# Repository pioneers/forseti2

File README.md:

forseti2
========
forseti2 (Named after the Norse god of justice) is PiE's third* iteration of a Field Control software. It has been in use from 2014-2017, with substantial changes along the way.

## Deploying Driver Stations
Driver Stations can be downloaded from PieCentral's [Releases section](https://github.com/pioneers/PieCentral/releases), or built locally using the `dawn/fieldcontrol` branch.

### Installing for MacOS and GNU/Linux
 1. Download the `darwin-x64` or `linux-x64` release anywhere (preferably desktop)
 2. In Terminal, run `driver_station.sh`
 3. Run Field Control Dawn

### Installing for Windows
 1. Download the `win32-ia32` release anywhere
 2. On the Desktop:
   * Create the file `bridge_address.txt` and write the Controller's IP address
   * Create the file `station_number.txt` and write the station number you want to be (0, 1, 2, 3 => blue1, blue2, gold1, gold2)
 3. Run Field Control Dawn

## Deploying Field Controller
forseti2 is dependent on external libraries, so there will be some OS-dependent instructions.

### [Lightweight Communications and Marshalling (LCM)](https://lcm-proj.github.io/)
1. Follow Online instructions on how to build it on your system.
2. Once LCM is built, move `lcm.jar` into the forseti2 directory to take advantage of `lcm-spy.sh` packet introspection.

### Installing for Ubuntu and MacOS
1. Install LCM as detailed above
2. If Ubuntu, also run:
```bash
sudo apt-get install arduino;
sudo pip install pyfirmata;
```

## Nodes
### timer.py
Maintains match state (timer and robot states)

#### Inputs
* Match/Init: Match
  * Resets match timer when a new match is initialized
* Timer/Control: TimeControl
  * Receives commands for the match timer (start, pause, reset)
* Robot[0-3]/Estop: Estop
  * Uses current emergency stop state and overrides all robot state if in estop mode
* Robot[0-3]/Override: Override
  * Determines whether or not robot is in manual override mode (overrides timers for manual operation)
* Robot[0-3]/RobotState: RobotState
  * Sets robot state using manual override only if in override mode

#### Outputs
* Timer/Time: Time
  * Publishes (every .3 secs) time elapsed in current match and stage, as well as the current stage name
* Robot[0-3]/RobotControl: RobotControl
  * Publishes (every .3 secs) the state of the robot (estop?, autonomous?, enabled?)

### lcm_ws_bridge.py
Bridges LCM to Websockets so JavaScript applications can access the network

### field_control.py
Manages electronics on the field

#### Inputs
* GameObjectTimer/LighthouseTime: LighthouseTime
  * Uses timer info to determine when to dump balls onto field
* Timer/Time: Time
  * Only dumps balls onto field during teleop and autonomous phases

#### Outputs
* Game_Button[0-1]/Button: Button
  * Publishes (every .3 secs) the state of a button
* Game_Motor[0-1]/Motor: Motor
  * Publishes (every .3 secs) the state of a motor

### heartbeat.py
Heartbeat for clients to confirm they are connected to the field network

#### Outputs
* Heartbeat/Beat: Heartbeat
  * Oscillates between True and False every second?

## Modifications to Dawn
* Listens to a specific Robot[0-3]/RobotControl channel and sends messages to robot accordingly
* Give meaningful feedback to field and students about robot connection status
* Display Field Information
  * Match state and timer
  * Heartbeat
* Manual start disabled in match

## Field Controller Information
### Network Monitor
* Displays live plots of messages/second on each channel

### Judge Console
* Allow score input for current match

### Field Console
* View robot states and allow for manual overriding and estop
* Allow control of match timer and robot enumeration (telling dawn to connect to robots)

### Stream Overlay
* Display field info (like dawn), scores, and upcoming matches

### Audience UI
* Like the stream overlay but as standalone webpage

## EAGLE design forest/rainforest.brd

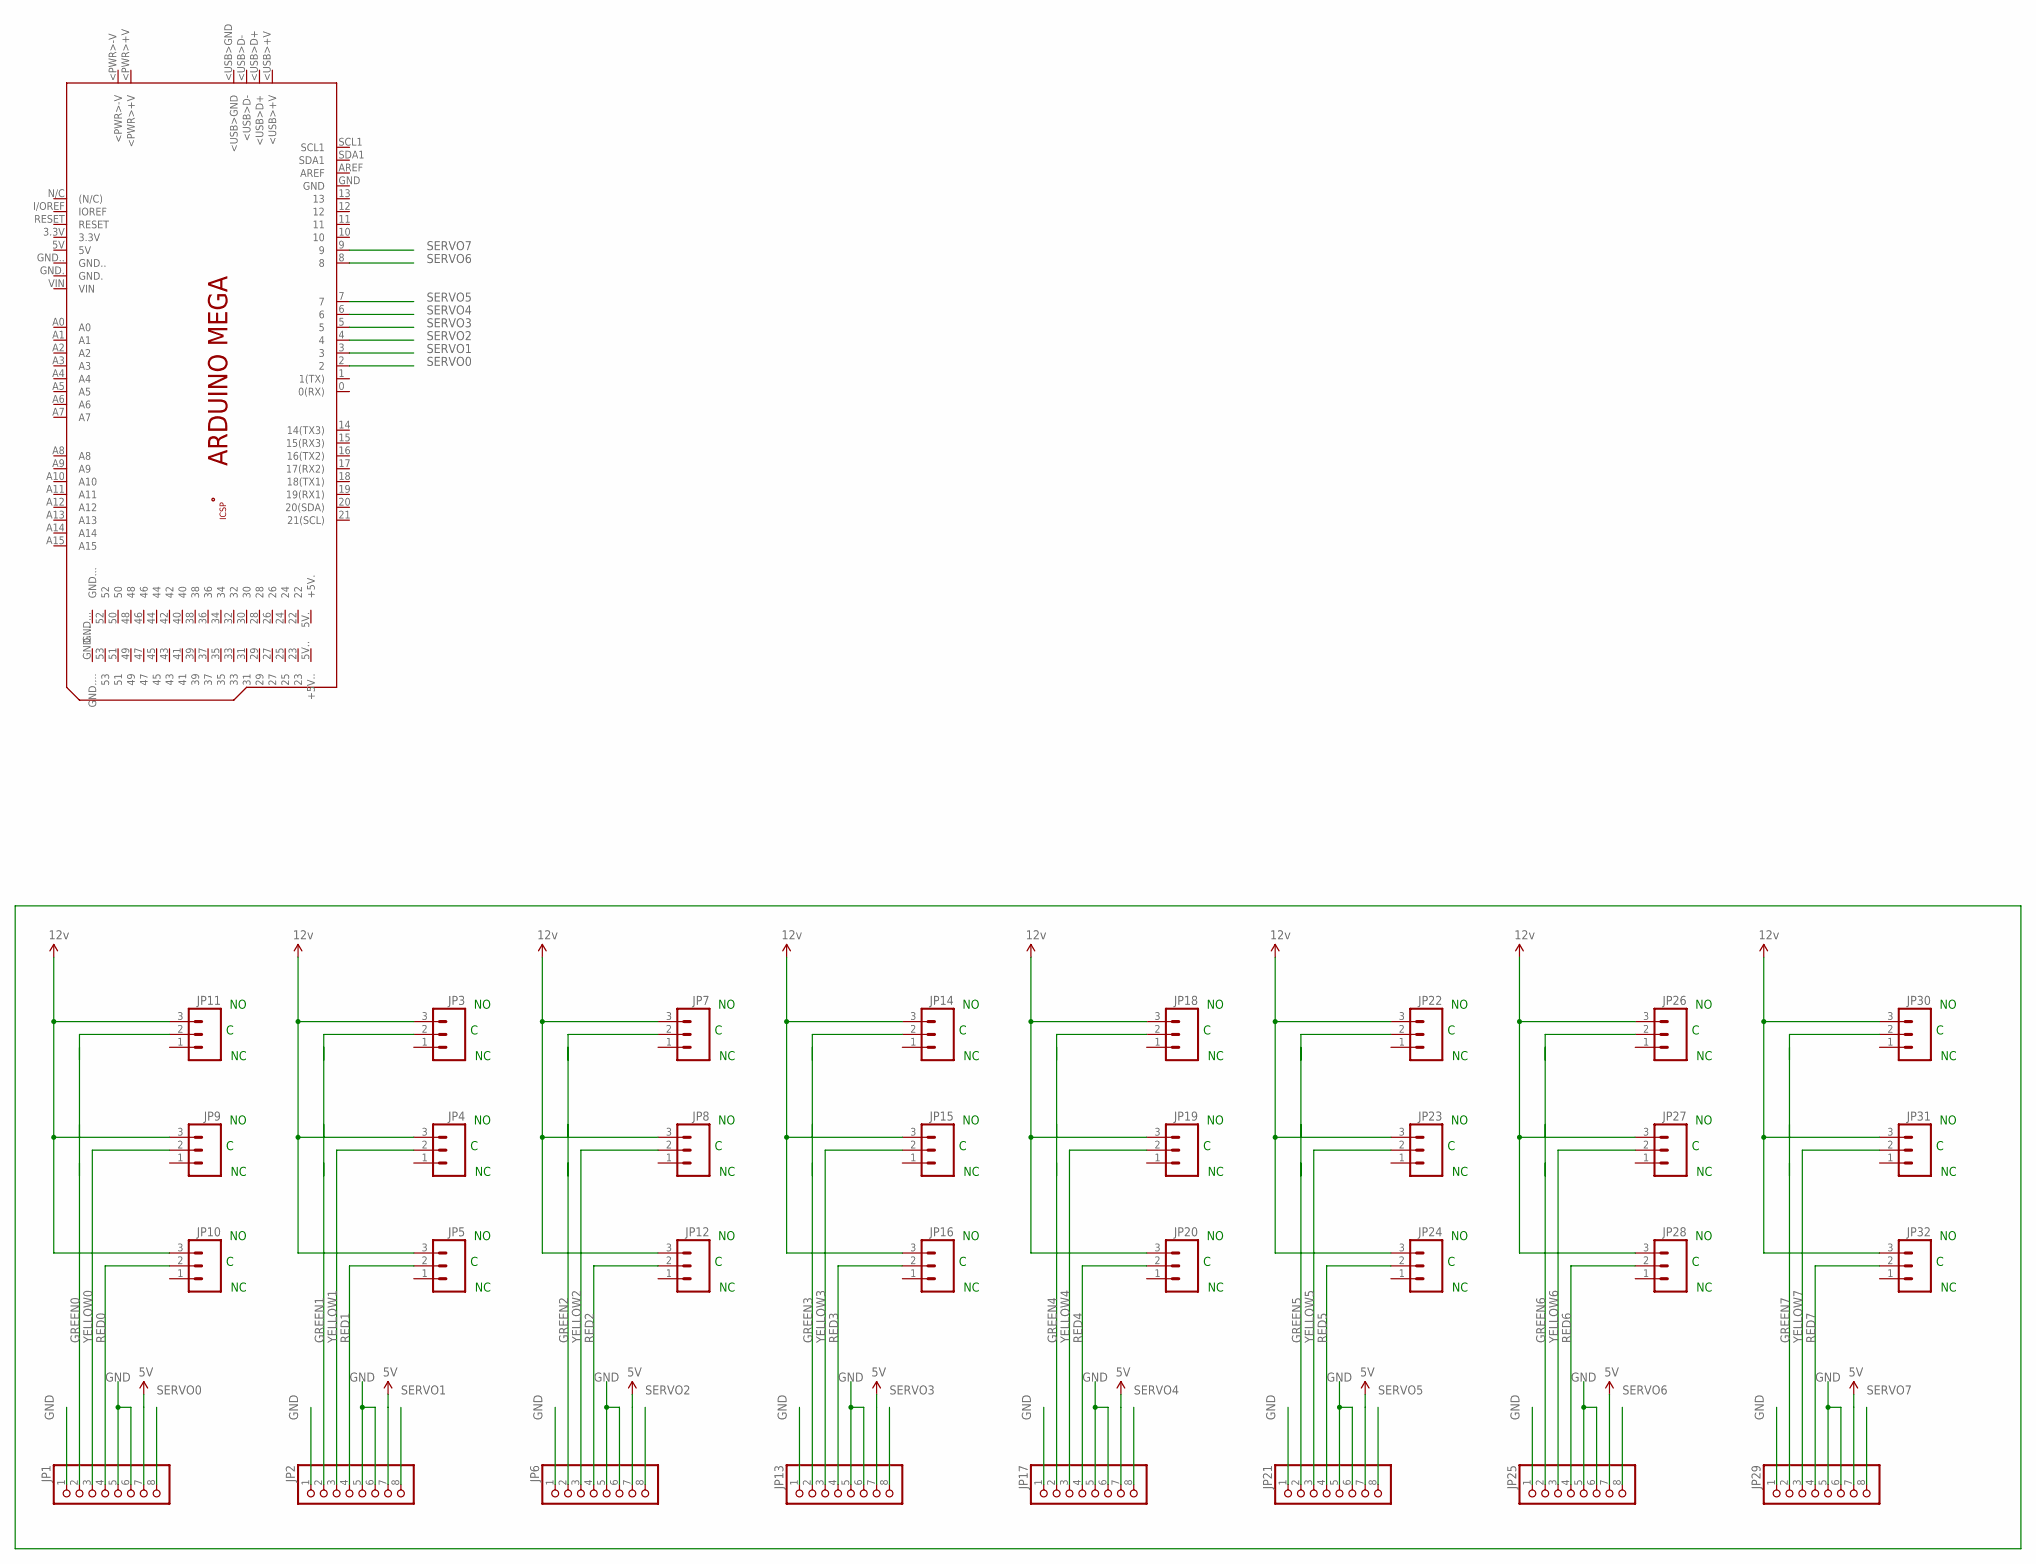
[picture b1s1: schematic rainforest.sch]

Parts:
JP1, JP2, JP6, JP13, JP17, JP21, JP25, JP29: PINHD-1X8; 1X08
JP3, JP4, JP5, JP7, JP8, JP9, JP10, JP11, JP12, JP14, JP15, JP16, JP18, JP19, JP20, JP22, JP23, JP24, JP26, JP27, JP28, JP30, JP31, JP32: M03PTH; 1X03
PCB1: ARDUINO_MEGA

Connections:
5V: JP1.7, JP2.7, JP6.7, JP13.7, JP17.7, JP21.7, JP25.7, JP29.7
12V: JP3.3, JP4.3, JP5.3, JP7.3, JP8.3, JP9.3, JP10.3, JP11.3, JP12.3, JP14.3, JP15.3, JP16.3, JP18.3, JP19.3, JP20.3, JP22.3, JP23.3, JP24.3, JP26.3, JP27.3, JP28.3, JP30.3, JP31.3, JP32.3
GND: JP1.1, JP1.5, JP1.6, JP2.1, JP2.5, JP2.6, JP6.1, JP6.5, JP6.6, JP13.1, JP13.5, JP13.6, JP17.1, JP17.5, JP17.6, JP21.1, JP21.5, JP21.6, JP25.1, JP25.5, JP25.6, JP29.1, JP29.5, JP29.6
GREEN0: JP1.2, JP11.2
GREEN1: JP2.2, JP3.2
GREEN2: JP6.2, JP7.2
GREEN3: JP13.2, JP14.2
GREEN4: JP17.2, JP18.2
GREEN5: JP21.2, JP22.2
GREEN6: JP25.2, JP26.2
GREEN7: JP29.2, JP30.2
RED0: JP1.4, JP10.2
RED1: JP2.4, JP5.2
RED2: JP6.4, JP12.2
RED3: JP13.4, JP16.2
RED4: JP17.4, JP20.2
RED5: JP21.4, JP24.2
RED6: JP25.4, JP28.2
RED7: JP29.4, JP32.2
SERVO0: JP1.8, PCB1.2
SERVO1: JP2.8, PCB1.3
SERVO2: JP6.8, PCB1.4
SERVO3: JP13.8, PCB1.5
SERVO4: JP17.8, PCB1.6
SERVO5: JP21.8, PCB1.7
SERVO6: JP25.8, PCB1.8
SERVO7: JP29.8, PCB1.9
YELLOW0: JP1.3, JP9.2
YELLOW1: JP2.3, JP4.2
YELLOW2: JP6.3, JP8.2
YELLOW3: JP13.3, JP15.2
YELLOW4: JP17.3, JP19.2
YELLOW5: JP21.3, JP23.2
YELLOW6: JP25.3, JP27.2
YELLOW7: JP29.3, JP31.2

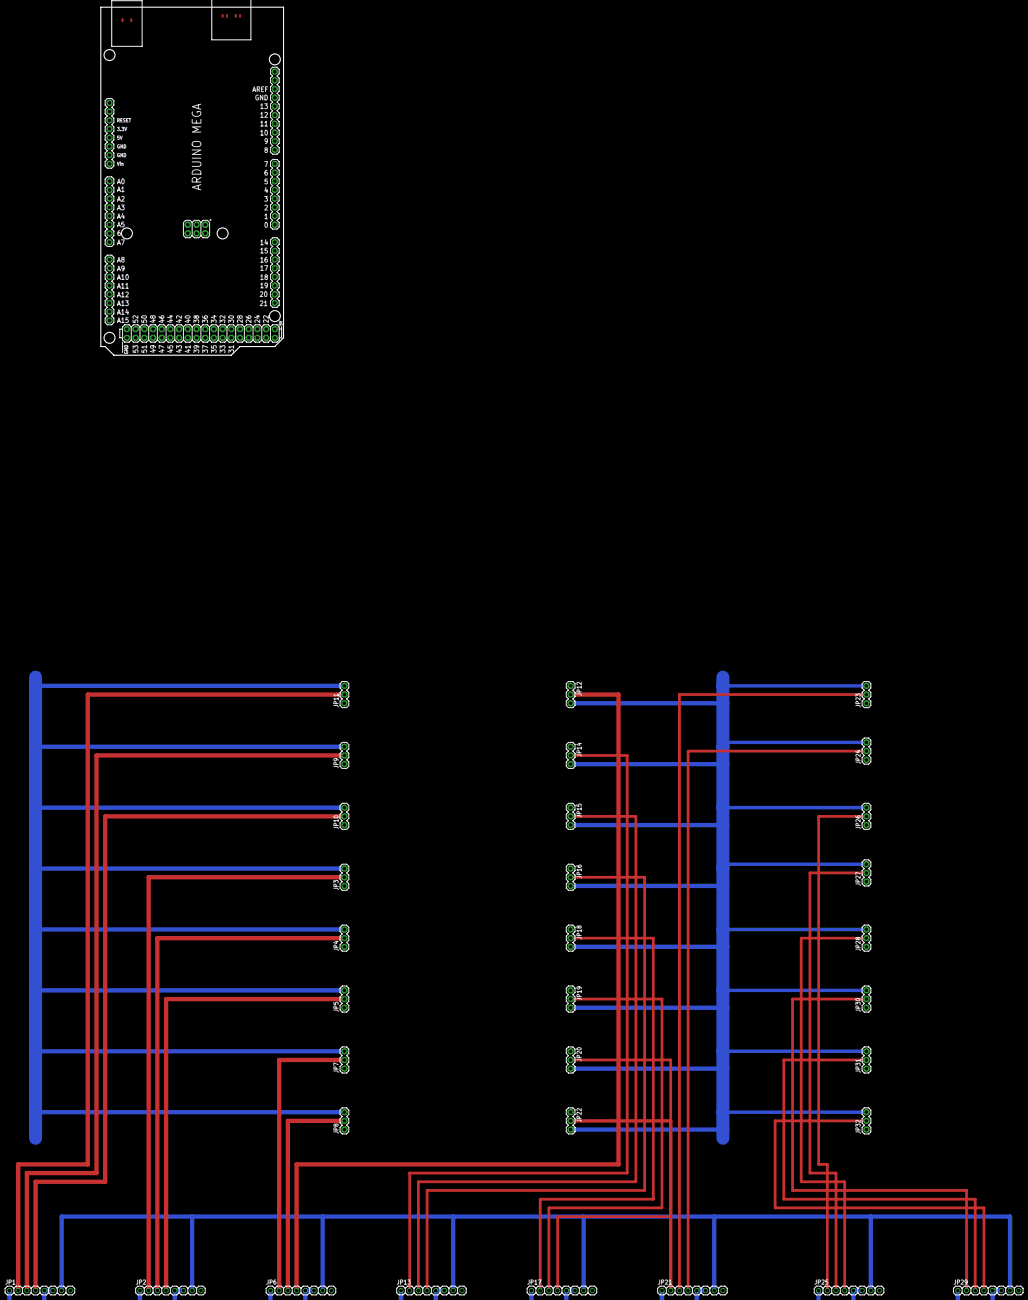
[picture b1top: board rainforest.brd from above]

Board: 2 copper layers, 53.3 x 101.6 mm, 33 parts (0 on the bottom side), 35 nets.

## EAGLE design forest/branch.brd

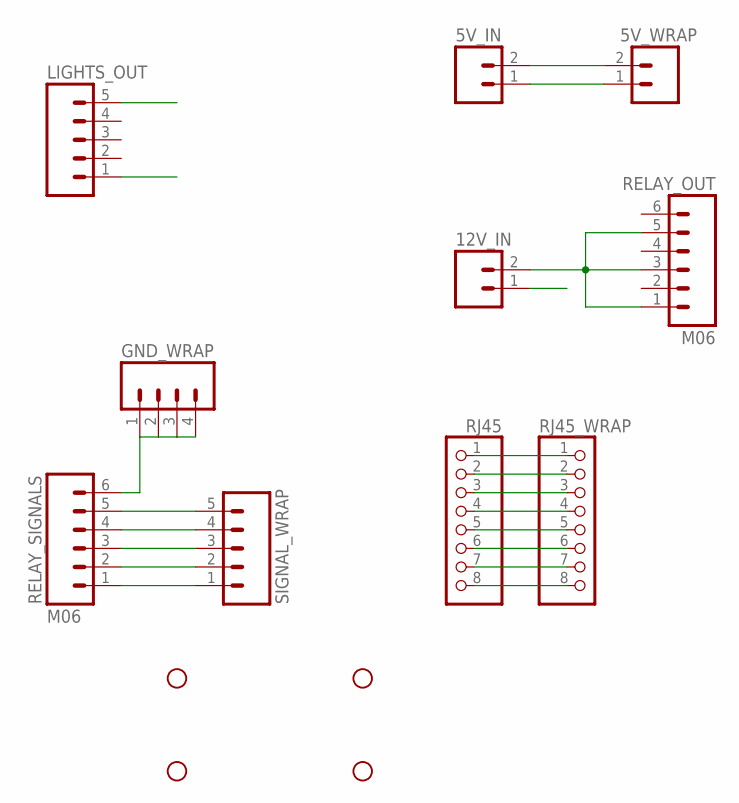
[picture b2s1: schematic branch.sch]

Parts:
5V_IN, 12V_IN: M021X02-MTA; 1X02-MTA
5V_WRAP: M02PTH; 1X02
GND_WRAP: M04PTH; 1X04
LIGHTS_OUT: M05MTA; 1X05-MTA
RELAY_OUT: M06; 1X06-MTA
RELAY_SIGNALS: M06; 1X06-MTA
RJ45, RJ45_WRAP: PINHD-1X8; 1X08
SIGNAL_WRAP: M05PTH; 1X05
STANDOFF1, STANDOFF2, STANDOFF3, STANDOFF4: STAND-OFF

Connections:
5V: 5V_IN.2, 5V_WRAP.2
12V: 12V_IN.2, RELAY_OUT.1, RELAY_OUT.3, RELAY_OUT.5
GND: 5V_IN.1, 5V_WRAP.1, 12V_IN.1, GND_WRAP.1, GND_WRAP.2, GND_WRAP.3, GND_WRAP.4, LIGHTS_OUT.1, RELAY_SIGNALS.6
unnamed: RELAY_SIGNALS.1, SIGNAL_WRAP.1
unnamed: RELAY_SIGNALS.2, SIGNAL_WRAP.2
unnamed: RELAY_SIGNALS.3, SIGNAL_WRAP.3
unnamed: RELAY_SIGNALS.4, SIGNAL_WRAP.4
unnamed: RELAY_SIGNALS.5, SIGNAL_WRAP.5
unnamed: RJ45.1, RJ45_WRAP.1
unnamed: RJ45.2, RJ45_WRAP.2
unnamed: RJ45.3, RJ45_WRAP.3
unnamed: RJ45.4, RJ45_WRAP.4
unnamed: RJ45.5, RJ45_WRAP.5
unnamed: RJ45.6, RJ45_WRAP.6
unnamed: RJ45.7, RJ45_WRAP.7
unnamed: RJ45.8, RJ45_WRAP.8
NC: LIGHTS_OUT.5

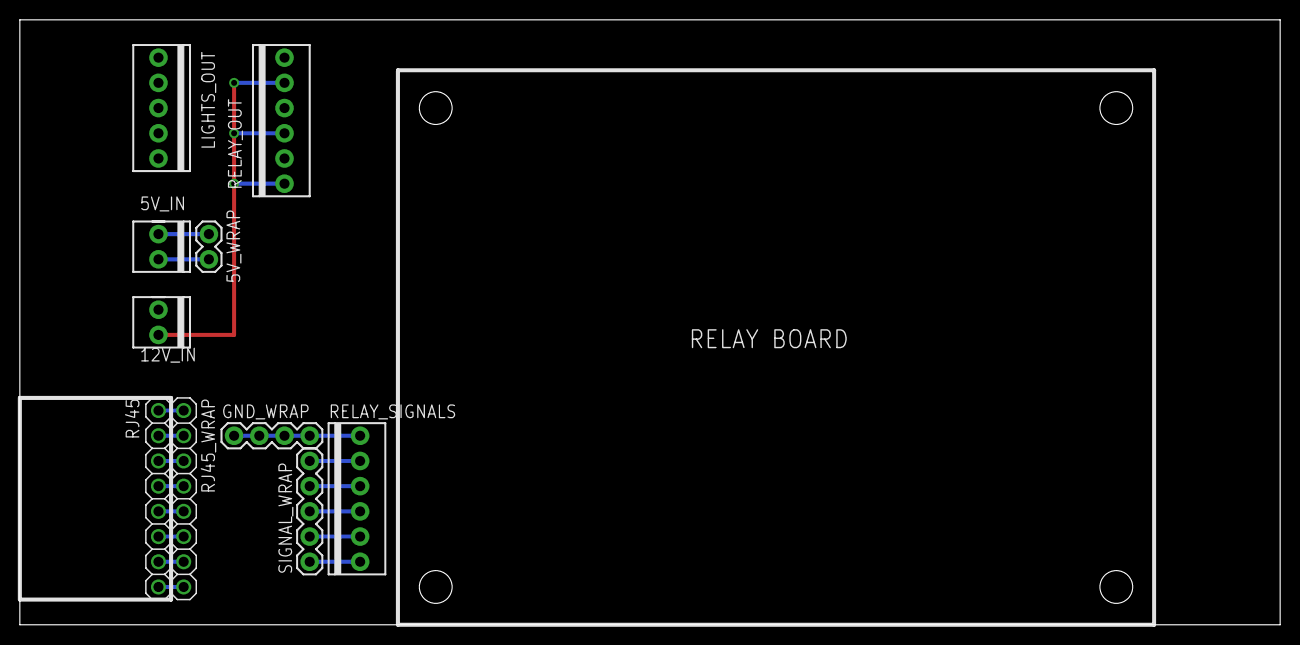
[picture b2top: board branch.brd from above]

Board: 2 copper layers, 127.0 x 61.0 mm, 14 parts (0 on the bottom side), 16 nets.

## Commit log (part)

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2013-12-24 Making explicit instructions in README.md
2013-12-24 added notice
2013-12-24 Update README.md
    added description and installation notes.
2014-01-28 added ipynb checkpoints to gitignore
2014-01-28 lcm simple message test working
2014-01-28 added broadcast/receive health scripts
2014-01-28 added header.lcm, fixed gen-types.sh, added cleanup.sh.
2014-01-29 added dispenser datatype, visualization, and testing routines.
2014-01-29 added dispenser servo control and servo test program
2014-02-01 Created fake piemos that spams health on "Piemos Health" and receives status on channel "To Piemos"
2014-02-05 added field_controller, which accepts field_cmds from robots and commands dispenser accordingly. added piemos_field_cmd type fixed dispenser_vis, dispensers visualized on incorrect side added simple 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
2014-02-05 removed ipython notebooks
2014-02-20 Fix pull request to use two FTDI/serial devices at once
2014-02-20 added lcm_nodes.dia: incomplete graph of lcm topic publishers, subscribers, and topic types and names
2014-02-22 added raspi admin scripts
2014-02-23 Created piemos controller to merge override and timer commands
2014-02-26 changes to write_sdcard
2014-03-17 added forest2 (electronics)
2014-03-17 added game_clocks and judge interface
2014-03-26 exposed time in test_piemos_controller.py
2014-03-26 started overdash.py
2014-03-27 added arduino firmata code for mega and firmata test
2014-03-27 das blinkin lights
2014-03-27 added forest driver
2014-03-27 updated readme with forest dependencies
2014-04-01 Add schematics and boards for branches
2014-04-03 untested prototype of override
2014-04-03 fixed overdash.py
2014-04-09 added lcm_unity
2014-04-09 fixed various issues in PR
2014-04-09 tentative piemos types
2014-04-09 Add README to explain the forseti2 folder
2014-04-09 Update dispenser visualization for the new forest protocol
2014-04-09 added needed flags to piemos_cmd
2014-04-09 piemos_health game time changed to int32
2014-04-09 cleanup added documentation and example use of configurator added settings.LCM_URI where missing added gamecontrol diagram
2014-04-10 fixed configurator out channels to match spec
2014-04-10 Implement xbox_driver.py
    Enables Xbox 360 controllers to publish their information.
2014-04-10 partial
2014-04-10 Implement OS X Compatibility layer
2014-04-10 Enable multiple controllers per driver server xbox_driver.py
2014-04-11 implement score_server.py to handle xbox commands
2014-04-11 Enforce maximum on permanent goal score
2014-04-11 Scoring system updates
    * Add and process a reset action in the delta message
    * Add a debug score client that can run all actions
    * Fix possession and score tracking for the bonus ball
2014-04-11 Change penalties to be per alliance, not per team
2014-04-11 Broadcast score_state messages to score/state
2014-04-11 Fix score total calculation
    * Remember to include permanent goal points in the total
    * Penalties decrease the score
2014-04-11 Re-enable saving in wxdash
2014-04-11 Integrate score display and submission button into timer/wxdash
2014-04-11 Add comments regarding purpose of enum values
2014-04-12 add jquery
2014-04-12 add comms_status
2014-04-12 implement first end-to-end
2014-04-12 add bootstrap
2014-04-12 super sketch template
2014-04-12 fix minor problems with interface
    simplify console
    fix game clock color update
2014-04-12 reindent html and add scoring section
2014-04-12 implement judge console connection status monitor
2014-04-12 refactor for readability
2014-04-12 implement miscellaneous system updates
    implement game-mode message processing
    store in global data container
    make loading bar right justified
    change gametime convention
2014-04-12 hyphenize urls
2014-04-12 add controller heartbeat to judge console
2014-04-12 Make requirements.txt more accurate
2014-04-12 Fix bug in util.LCMSequence
2014-04-12 implement basic scoring feedback
2014-04-12 implement point display on judge console
2014-04-12 make guide button control judge console controller heartbeat
2014-04-12 Initial implementation of field controller
    Modernize test that simulates PiEMOS
    Remove deprecated dispenser_cmd packet type
2014-04-12 Move game phase time values into settings.py
2014-04-12 Integrate field_controller with timer.py
    * Get RFID card data by listening to "Match/Init"
    * Release teleop dispensers and unrelease during field reset by
    listening to "piemos/Control"
2014-04-12 integrate judge console with timer.py
2014-04-12 added match and config downloaders, and tested config downloader
2014-04-13 implement misc judge ux changes
2014-04-13 implement judge console team name display
2014-04-13 improve formatting in judge console Scoring module
2014-04-13 Fix xbox_score_client to accept a channel name, not joystick number
2014-04-13 Script to start all field control nodes in a tmux window
2014-04-13 Add RFID tag data for sets of tags
2014-04-13 Penalize alliances for over-possession of the bonus ball
2014-04-13 Basic score adjustment HTML page
2014-04-13 implement score adjustment in judge console, also removed extra form
2014-04-13 fixed sending configs to piemos + other stuff
2014-04-13 Add scheduler.py to nodes.yml
2014-04-13 Swap uid and tagId fields in the json files
2014-04-13 Fix incorrectly scanned rfid uids
2014-04-13 Reset bad rfid timers at the start of each match
2014-04-13 refactor judge_console.js and change Flask settings to pseudo-production
2014-04-13 Better lights control
    Flash green lights when teleoperated goals released
    Turn on orange lights when robots are disabled
    Turn on red lights when robots are not connected
2014-04-13 Add overdash.py to nodes.yml
2014-04-13 Fix reversed alliances in activate_lights_team
2014-04-13 Send forest command when updating lights based on piemos health
2014-04-13 Better green light flashing for dispenser release
    * Avoid lights being stuck to green during all of teleop
    * Keep green light on for 6 seconds
2014-04-13 clock system
2014-04-13 more clock
2014-04-13 even more clock
2014-04-13 Lights update
    * Also turn on red light if PiEMOS is not sending health packets
    * Activate orange lights anytime the robot is disabled
2014-04-13 listen on all ports
2014-04-13 Fixups for field_controller
2014-04-13 Include autonomous score in the score data types
2014-04-13 Include bonus ball time remaining until penalty in the score_state
2014-04-13 Make initial match score 2-2, not 0-0
2014-04-13 enable bonus ball timer
2014-04-15 Changed forest vis to reflect the status of the lights and servo. Might still need more text to clarify UI
2014-04-15 Cleaned up code. Changed default state. Go to sleep andrew chen
2014-04-16 implement xbox_driver.py only sends packets when it has changed buttons
2014-04-16 update README with actual stuff
2014-04-17 Schematics and layout for forest3 rainy
2014-04-18 LCM WebSocket bridge
2014-04-19 Adjusted forest driver and firmata to reflect pin changes on forest3, rainy
2014-04-19 removed sleeps in config sending
2014-04-20 Alternative xbox controller driver
    This is an alternative xbox controller driver based on the grizzly bear testing
    code. Unlike the pygame-based driver, it can control the LEDs on the front of
    the controller.
    This allows the judge controllers to be distinguishable on sight:
    * LED #1 is lit for the blue alliance ref
    * LED #2 is lit for the gold alliance ref
2014-04-20 Switch to alternative xbox driver, and autostart all 3 joystick nodes
2014-04-20 Fix score server handling of excess permanent goal points
    Previously, it would cap the maximum score for the permanent goal, but keep
    decrementing the opposing alliances' score as if a ball had left one side of
    the field.
    Now the entire score delta packet is ignored.
2014-04-20 Make points assessment for dispenser balls entering the field automatic
    If the score must be adjusted to account for unreleased dispensers, that can be
    done manually
2014-04-20 Brute-force kill all extra xboxdrv instance when shutting down
    Shutting down xbox_driver_alternative.py leaves behind processes that keep
    control of the USB ports and don't let another xbox driver start correctly.
    This is technically not the right way to do it because it can kill nodes running
    in another terminal, but it enables easier restarts of field control.
2014-04-20 Fix incorrect data being sent in judge_flask
2014-04-20 Add adjustments for autonomous points to the dashboard
2014-04-20 Better score adjustment interface
2014-04-26 include permanent points in points
2014-04-26 fixed something broken
2014-04-26 send actual score values instead of sending them all in autonomous
2014-04-26 force https on match upload
2014-04-26 Fix bonus ball score submission
2014-04-26 Remove extra field in score submision
    The "number" field is the POST request is not used, so it should be removed to avoid confusion.
2014-04-26 added team names to overlay bar
2014-04-26 add match number
2014-04-26 reverse bar
2014-05-01 on-day fixes at final competition
2016-02-10 create network monitor app
2016-02-11 update lcm bridge to allow reconnecting
2016-02-13 implement heartbeat
2016-02-18 create RobotControl message
2016-02-18 Made lighthouse timer
2016-02-18 implement robot_controller.py
2016-02-20 initial button+motor with monitor
2016-02-20 lcm files for button and motor
2016-02-20 Modified field_control.py and GameobjectTimer
2016-02-20 Got field_control to work
2016-02-20 Renamed channels, updated monitor
2016-02-20 field_control tested packets sending working
2016-02-22 fix minor issues
2016-02-25 Made changes to gameObjectTimer
2016-03-03 rename randNum to counter
2016-03-03 motor + button update
2016-03-10 run memcached and add hibike to path so runtime doesn't crash
2016-03-10 add button test script
2016-03-10 Changed gameobjecttimer to lighthousetimer
2016-03-13 refactor lighthouse logic
2016-03-17 begin implementation of live scoring
2016-03-22 style scoring ui
2016-03-22 upload pages
2016-03-31 create uis
2016-03-31 added Status lights
2016-04-01 implement monolithic status light driver
2016-04-01 clean up field_control.py
2016-04-01 move index to ui folder
2016-04-02 create driver station script
2016-04-02 move driver station script
2016-04-02 add driver station incantation
2016-04-02 fix typo in readme
2016-04-02 typo in script
2016-04-02 switch to node 5.0
2016-04-02 add if to lcm
2016-04-02 add tornado to script
2016-04-02 add network command to driver station
2016-04-03 add wifi script
2016-04-05 add notes
2016-04-05 begin implementing robot control ui
2016-04-07 Competition Scheduler for field control
2016-04-07 remove networking from driver station script
2016-04-07 add running variable to robot state
2016-04-09 seperate status light logic
2016-04-09 Added driver light status
2016-04-09 Forgot RobotStatus struct
2016-04-14 move off of CDN
2016-04-14 Added sound to be played after match ends
2016-04-21 update robot_control.html to reflect new runtime changes
2016-04-21 Play sounds
2016-04-21 Implement populating match info from spreadsheet
2016-04-22 update souds and shooter controls
2016-04-22 add lighthouse sounds
2016-04-22 create arduino shooter control lcm node
2016-04-22 make scoreboard larger for stream
2016-04-23 Have script prompt for config info
2016-04-23 hardcode bridge addr
2016-04-23 faster clocks
2016-04-23 update scoreboard to use allens css
2016-04-23 Refetch spreadsheet data when loading
2016-04-23 add post match scoreboard to navbar
2016-04-23 add adjustment to livescoring
2016-04-23 update title of post match ui
2016-04-23 move ui to root for gh-pages
2017-04-13 Upgrade for newer teamocil version
2017-04-15 Remove Lighthouse timer bar and change matches to reference matchdb.js
2017-04-15 Remove Lighthouse timer bar and change matches var to reference matchdb.js
2017-04-15 Add nojekyll file
2017-04-15 Change live scoring functions
2017-04-29 Remove lighthouse bars and change match db
2017-04-29 Update spreadsheet links
2017-04-29 Start of README Rewrite for 2017 (#51)
    * README Rewrite for 2017
    * Update Readme with better Bash Script
    * Rewrite driver_station.sh, cleanup unused instructions
2017-04-29 Add architecture notes (#52)
2017-04-29 Fix scoring
